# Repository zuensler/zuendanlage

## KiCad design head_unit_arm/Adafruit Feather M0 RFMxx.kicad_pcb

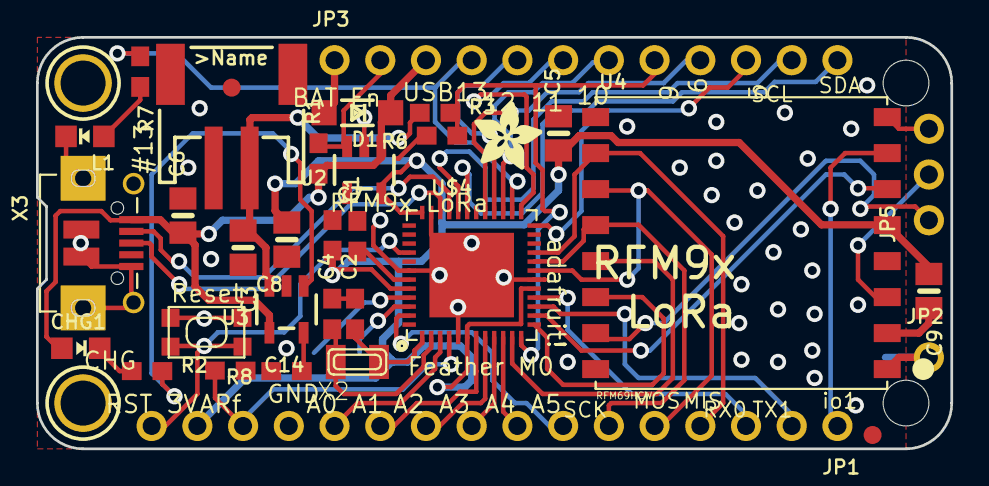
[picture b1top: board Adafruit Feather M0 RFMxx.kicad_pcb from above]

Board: 2 copper layers, 50.8 x 22.9 mm, 44 parts (0 on the bottom side), 46 nets.

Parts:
@HOLE0, @HOLE1: (no value)
C1, C7, C14: 1uF; 0603-NO
C2, C4: 22pF; 0603-NO
C3, C6, C8: 10µF; 0805-NO
C5, C9: 10uF; 0805-NO
CHG1: ORANGE; CHIPLED_0805_NOOUTLINE
D1: MBR120; SOD-123
JP1: HEADER-1X16ROUND; 1X16_ROUND
JP2: HEADER-1X1ROUND; 1X01_ROUND
JP3: HEADER-1X12; 1X12_ROUND
JP5: HEADER-1X3ROUND; 1X03_ROUND
L1: RED; CHIPLED_0805_NOOUTLINE
R1, R3: 100k; 0603-NO
R2: 1K; 0603-NO
R6: 100K; 0603-NO
R7: 2.2K; 0603-NO
R8: 10K\; 0603-NO
SW1: SPST_TACT-KMR2; KMR2
TP1, TP2: TESTPOINTROUND1.5MM; TESTPOINT_ROUND_1.5MM
U2: AP2112K-3.3; SOT23-5
U3: MCP73831T-2ACI/OT; SOT23-5
U4: RFM69HCW; RFMHCW_SMT
U$4: ATSAMD21G18_QFN; TQFN48_7MM
U$7, U$12: ADAFRUIT_3.5MM
U$9: FEATHERLOGO
U$13: PCBFEAT-REV-040
U$31, U$32: MOUNTINGHOLE2.5; MOUNTINGHOLE_2.5_PLATED
U$34, U$35: FIDUCIAL; FIDUCIAL_1MM
X1: JSTPH; JSTPH2
X2: 32.768; XTAL3215
X3: microUSB; 4UCONN_20329_V2
X4: uFL; U.FL

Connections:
+3V3: C5.1, C7.1, C8.1, C9.1, JP1.15, U2.5, U4.5P, U$4.6, U$4.17, U$4.36, U$4.44
/A0: JP1.12, U$4.3
/A1: JP1.11, U$4.7
/A2: JP1.10, U$4.8
/A3: JP1.9, U$4.9
/A4: JP1.8, U$4.10
/A5: JP1.7, U$4.47
/AREF: C14.1, JP1.14, U$4.4
/D0: JP1.3, U$4.16
/D1: JP1.2, U$4.15
/D3_IRQ: U4.6P, U$4.14
/D4_RST: U4.14P, U$4.13
/D5: JP3.10, U$4.24
/D6: JP3.9, U$4.29
/D8_CS: U4.13P, U$4.11
/D9: JP3.8, R3.2, R6.1, U$4.12
/D10: JP3.7, U$4.27
/D11: JP3.6, U$4.25
/D12: JP3.5, U$4.28
/D13: JP3.4, R7.1, U$4.26
/D+: U$4.34, X3.D+
/D-: U$4.33, X3.D-
/DIO1: JP1.1, U4.7P
/DIO2: JP5.3, U4.8P
/DIO3: JP5.2, U4.3P
/DIO5: JP5.1, U4.15P
/EN: JP3.2, R1.2, U2.3
/MISO: JP1.4, U4.10P, U$4.21
/MOSI: JP1.5, U4.11P, U$4.19
/SCK: JP1.6, U4.12P, U$4.20
/SCL: JP3.11, U$4.32
/SDA: JP3.12, U$4.31
/SWCLK: TP1.P$1, U$4.45
/SWDIO: TP2.P$1, U$4.46
/~RESET: JP1.16, SW1.1, SW1.3, U$4.40
GND: C1.2, C2.2, C3.2, C4.2, C5.2, C6.2, C7.2, C8.2, C9.2, C14.2, JP1.13, L1.C, R6.2, R8.2, SW1.2, SW1.4, U2.2, U3.2, U4.2P, U4.9P, U4.16P, U$4.5, U$4.18, U$4.35, U$4.42, U$4.THERMAL, X1.1, X3.BASE@1, X3.BASE@2, X3.GND, X3.SPRT@1, X3.SPRT@2, X3.SPRT@3, X3.SPRT@4, X4.1, X4.2
unnamed: C1.1, U$4.43
unnamed: C2.1, U$4.1, X2.P$1
unnamed: C4.1, U$4.2, X2.P$2
unnamed: CHG1.C, R2.1
unnamed: JP2.1, U4.1P, X4.3
unnamed: L1.A, R7.2
unnamed: R2.2, U3.1
unnamed: R8.1, U3.5
VBAT: C3.1, D1.A, JP3.1, R3.1, U3.3, X1.2
VBUS: C6.1, CHG1.A, D1.C, JP3.3, R1.1, U2.1, U3.4, X3.VBUS

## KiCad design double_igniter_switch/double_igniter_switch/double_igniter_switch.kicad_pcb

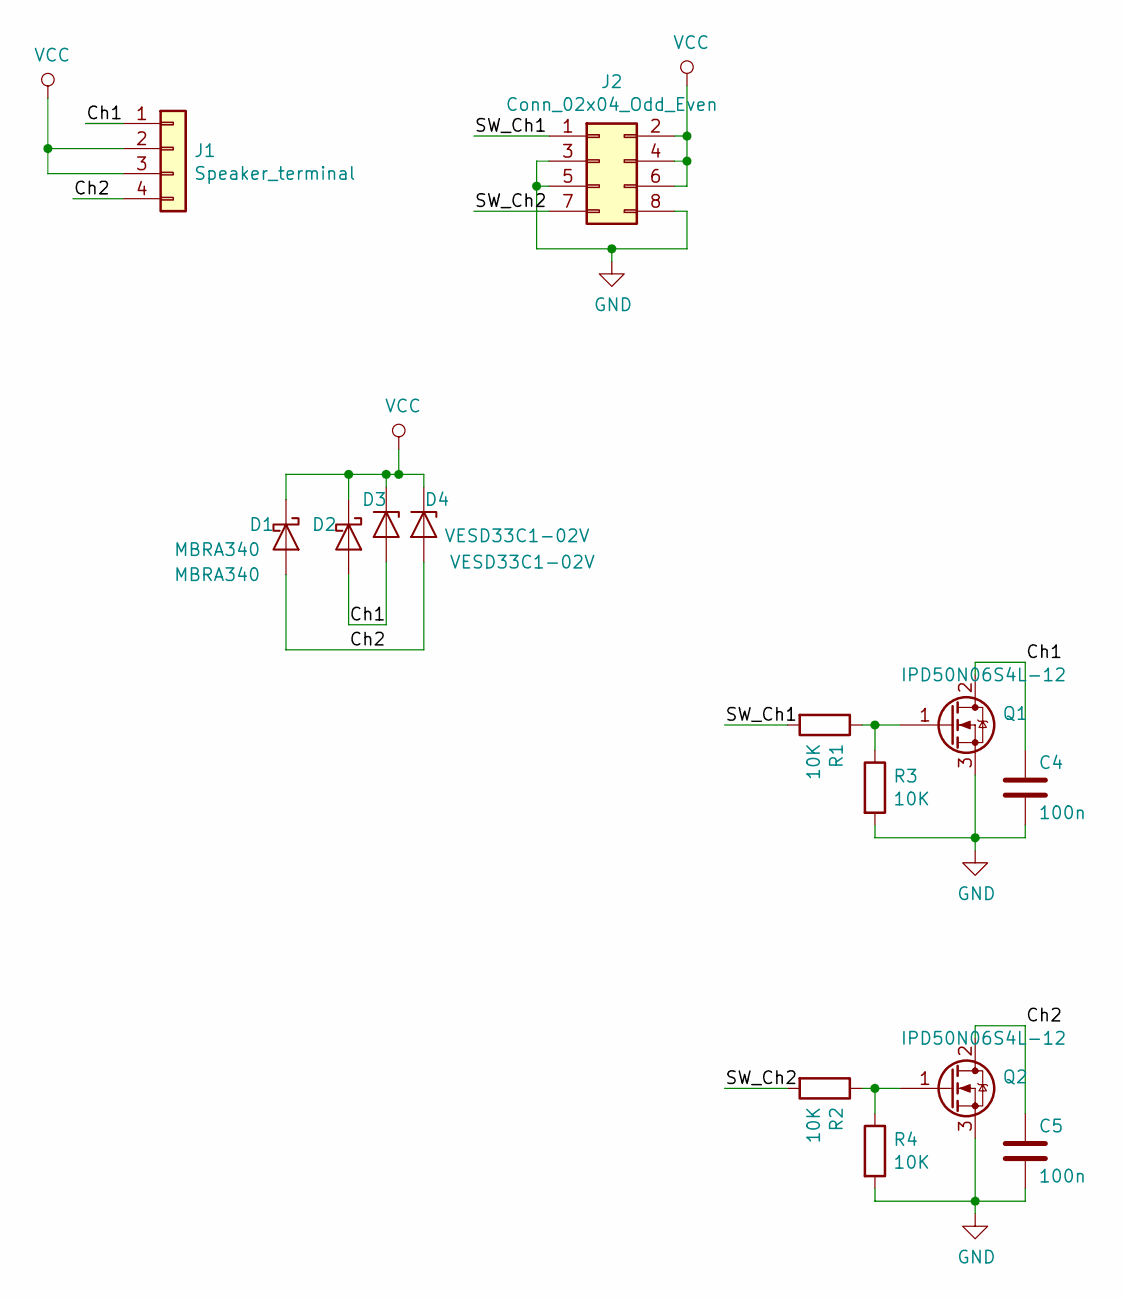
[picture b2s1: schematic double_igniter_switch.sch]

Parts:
C4, C5: 100n; R_1206_3216Metric
D1, D2: MBRA340; D_SMA
D3, D4: VESD33C1-02V; D_SOD-523
J1: Speaker_terminal; speaker_terminal
J2: Conn_02x04_Odd_Even; PinHeader_2x04_P2.54mm_Horizontal
Q1, Q2: IPD50N06S4L-12; TO-252-2
R1, R2, R3, R4: 10K; R_1206_3216Metric

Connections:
/Ch1: C4.2, D2.2 (A), D3.2 (A), J1.1, Q1.2 (D)
/Ch2: C5.2, D1.2 (A), D4.2 (A), J1.4, Q2.2 (D)
/SW_Ch1: J2.1, R1.2
/SW_Ch2: J2.7, R2.2
GND: C4.1, C5.1, J2.3, J2.5, J2.8, Q1.3 (S), Q2.3 (S), R3.2, R4.2
unnamed: Q1.1 (G), R1.1, R3.1
unnamed: Q2.1 (G), R2.1, R4.1
VCC: D1.1 (K), D2.1 (K), D3.1 (K), D4.1 (K), J1.2, J1.3, J2.2, J2.4, J2.6

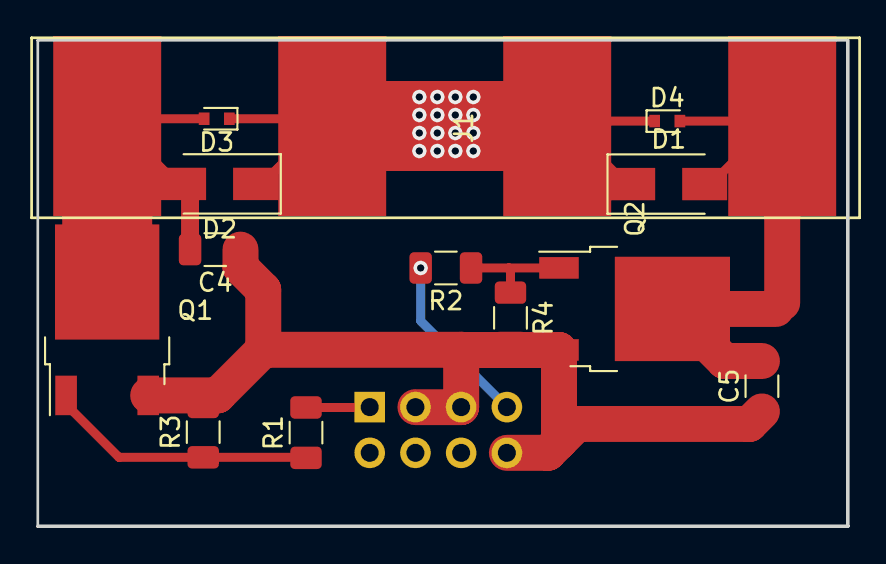
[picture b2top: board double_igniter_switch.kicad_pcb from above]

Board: 2 copper layers, 45.0 x 27.0 mm, 14 parts (1 on the bottom side), 8 nets.

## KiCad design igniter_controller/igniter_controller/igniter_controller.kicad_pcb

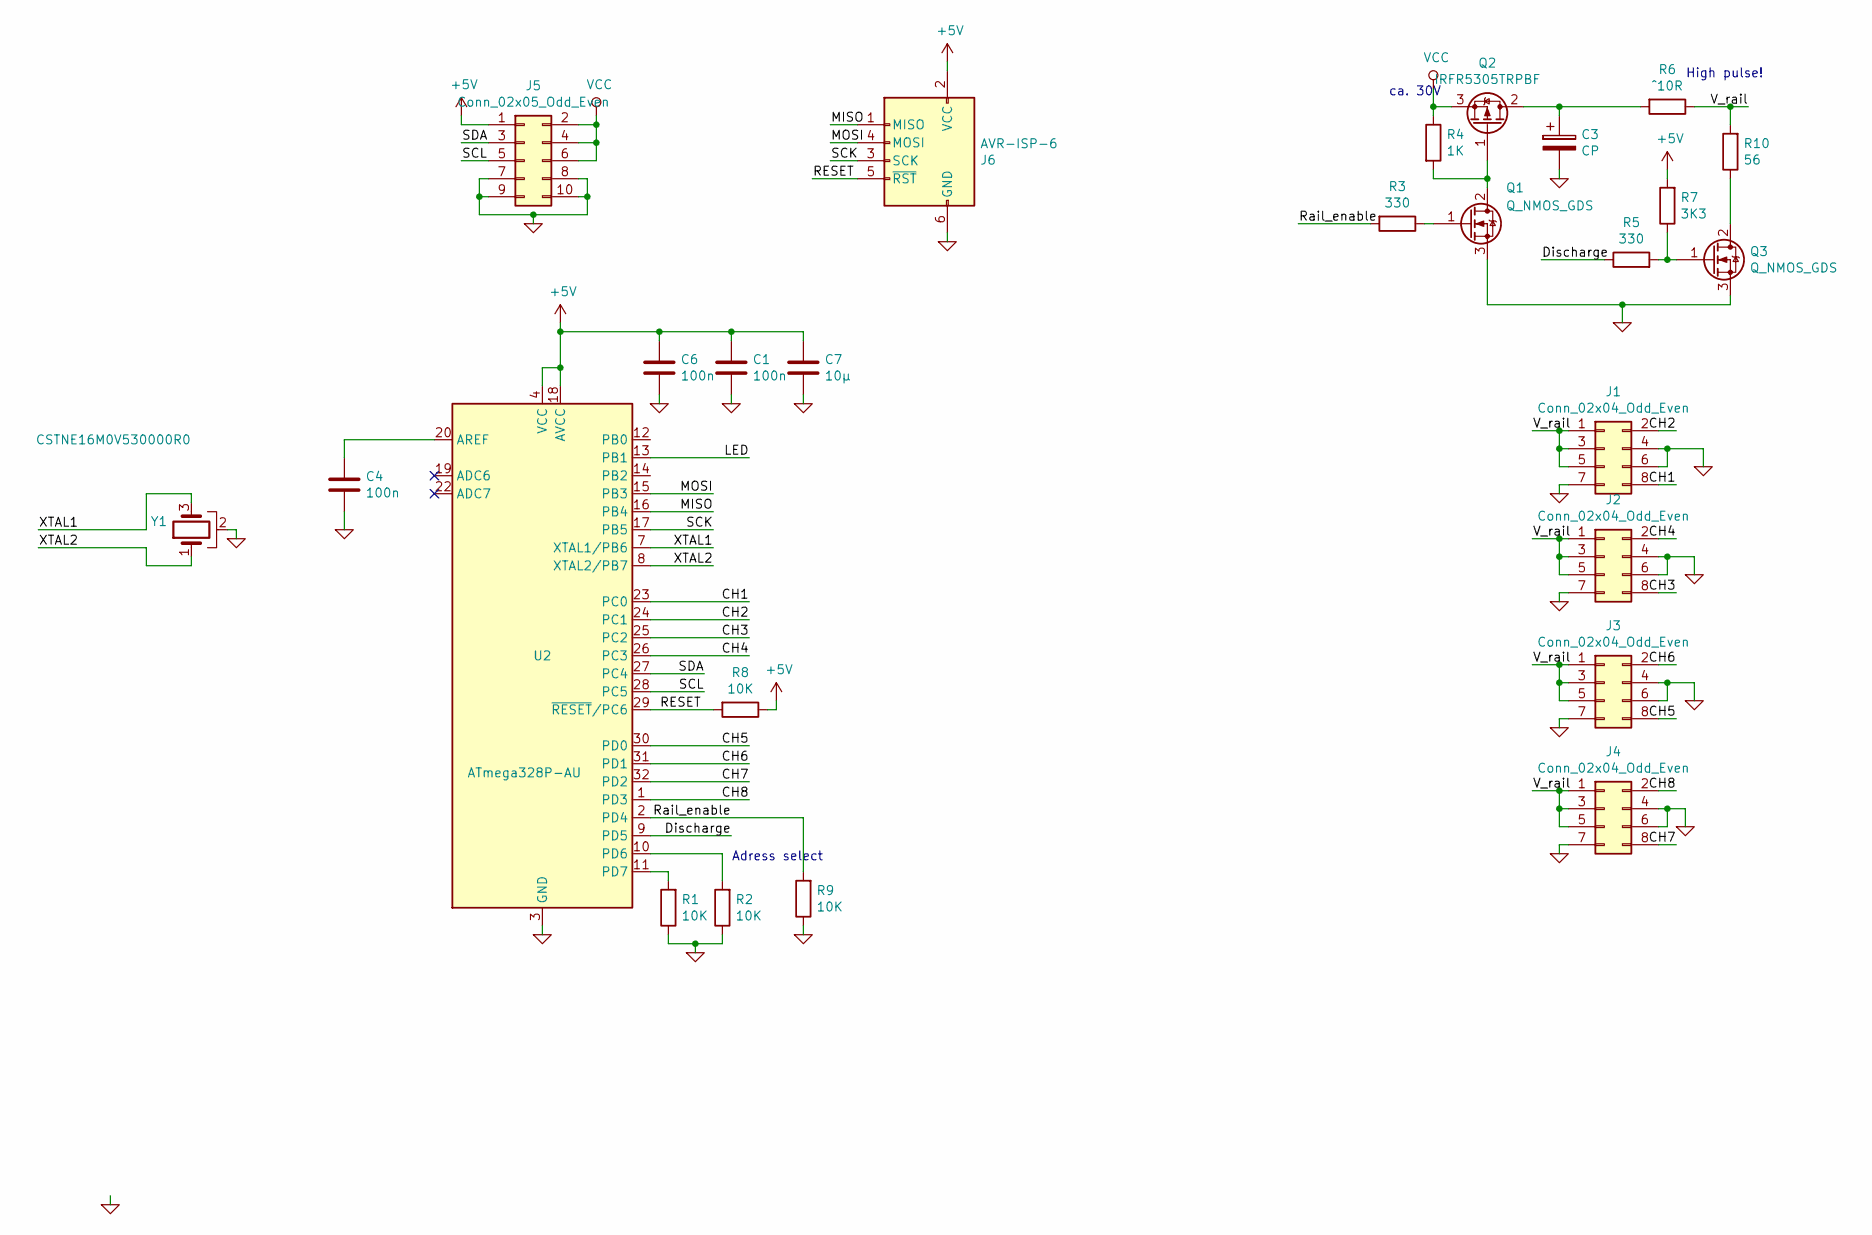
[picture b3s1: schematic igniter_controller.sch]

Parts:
C1, C4, C6: 100n; C_0603_1608Metric
C3: CP; C_Radial_D16.0mm_H31.5mm_P7.50mm
C7: 10µ; R_1206_3216Metric
J1, J2, J3, J4: Conn_02x04_Odd_Even; PinSocket_2x04_P2.54mm_Vertical
J5: Conn_02x05_Odd_Even; PinHeader_2x05_P2.54mm_Vertical
J6: AVR-ISP-6; PinHeader_2x03_P2.54mm_Vertical
Q1, Q3: Q_NMOS_GDS; SOT-23
Q2: IRFR5305TRPBF; TO-252-2
R1, R2, R8, R9: 10K; R_0603_1608Metric
R3, R5: 330; R_0603_1608Metric_Pad1.05x0.95mm_HandSolder
R4: 1K; R_0603_1608Metric_Pad1.05x0.95mm_HandSolder
R6: ^10R; R_1206_3216Metric
R7: 3K3; R_0603_1608Metric
R10: 56; R_1206_3216Metric
U2: ATmega328P-AU; TQFP-32_7x7mm_P0.8mm
Y1: CSTNE16M0V530000R0; Resonator_SMD_muRata_CSTxExxV-3Pin_3.0x1.1mm

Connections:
+5V: C1.1, C6.1, C7.1, J5.1, J6.2 (VCC), R7.2, R8.1, U2.4 (VCC), U2.6 (VCC), U2.18 (AVCC)
/CH1: J1.8, U2.23 (PC0)
/CH2: J1.2, U2.24 (PC1)
/CH3: J2.8, U2.25 (PC2)
/CH4: J2.2, U2.26 (PC3)
/CH5: J3.8, U2.30 (PD0)
/CH6: J3.2, U2.31 (PD1)
/CH7: J4.8, U2.32 (PD2)
/CH8: J4.2, U2.1 (PD3)
/Discharge: R5.1, U2.9 (PD5)
/MISO: J6.1 (MISO), U2.16 (PB4)
/MOSI: J6.4 (MOSI), U2.15 (PB3)
/RESET: J6.5 (~RST), R8.2, U2.29 (~RESET~/PC6)
/Rail_enable: R3.2, R9.2, U2.2 (PD4)
/SCK: J6.3 (SCK), U2.17 (PB5)
/SCL: J5.5, U2.28 (PC5)
/SDA: J5.3, U2.27 (PC4)
/V_rail: J1.1, J1.3, J1.5, J2.1, J2.3, J2.5, J3.1, J3.3, J3.5, J4.1, J4.3, J4.5, R6.1, R10.2
/XTAL1: U2.7 (XTAL1/PB6), Y1.3
/XTAL2: U2.8 (XTAL2/PB7), Y1.1
GND: C1.2, C3.2, C4.2, C6.2, C7.2, J1.4, J1.6, J1.7, J2.4, J2.6, J2.7, J3.4, J3.6, J3.7, J4.4, J4.6, J4.7, J5.7, J5.8, J5.9, J5.10, J6.6 (GND), Q1.3 (S), Q3.3 (S), R1.1, R2.1, R9.1, U2.3 (GND), U2.5 (GND), U2.21 (GND), Y1.2
unnamed: C3.1, Q2.2 (D), R6.2
unnamed: C4.1, U2.20 (AREF)
unnamed: Q1.1 (G), R3.1
unnamed: Q1.2 (D), Q2.1 (G), R4.2
unnamed: Q3.1 (G), R5.2, R7.1
unnamed: Q3.2 (D), R10.1
unnamed: R1.2, U2.11 (PD7)
unnamed: R2.2, U2.10 (PD6)
VCC: J5.2, J5.4, J5.6, Q2.3 (S), R4.1

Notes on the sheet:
Adress select
High pulse!
ca. 30V

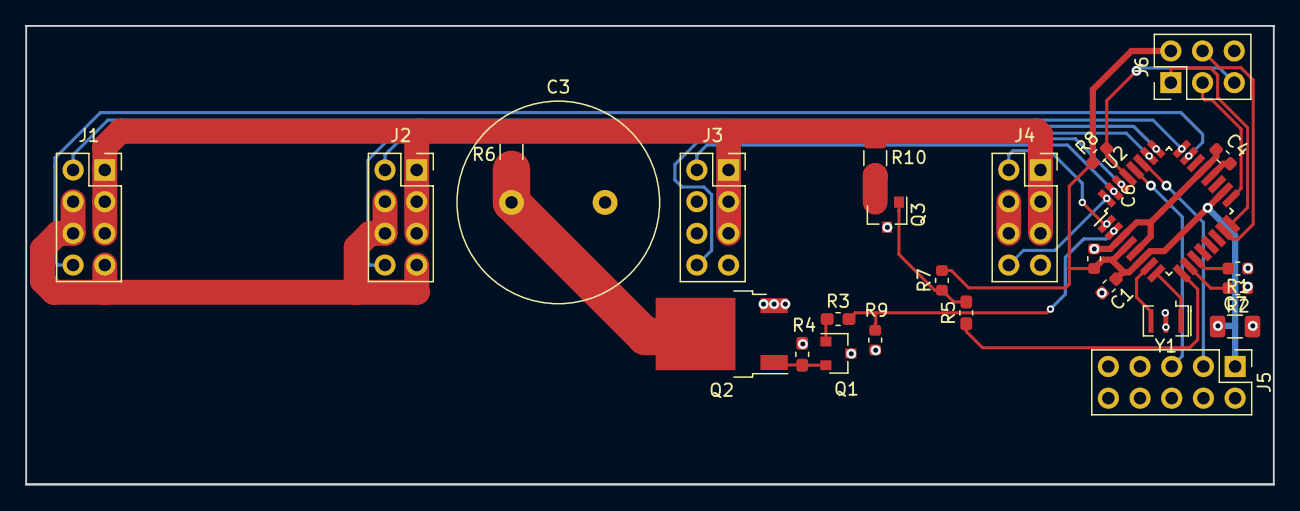
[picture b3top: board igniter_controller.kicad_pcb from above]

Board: 2 copper layers, 100.0 x 36.8 mm, 26 parts (0 on the bottom side), 30 nets.

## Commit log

2019-09-21 started with schema for switch module
2019-09-22 added layout for igniter switch
2019-09-25 added expander board with layout
2019-09-25 added esd diode and free wheeling dioed to mosfet module, removed gate drive, changed pinout
2019-09-26 startet with esp circuit for head unit
2019-09-26 added board with head unit and supply
